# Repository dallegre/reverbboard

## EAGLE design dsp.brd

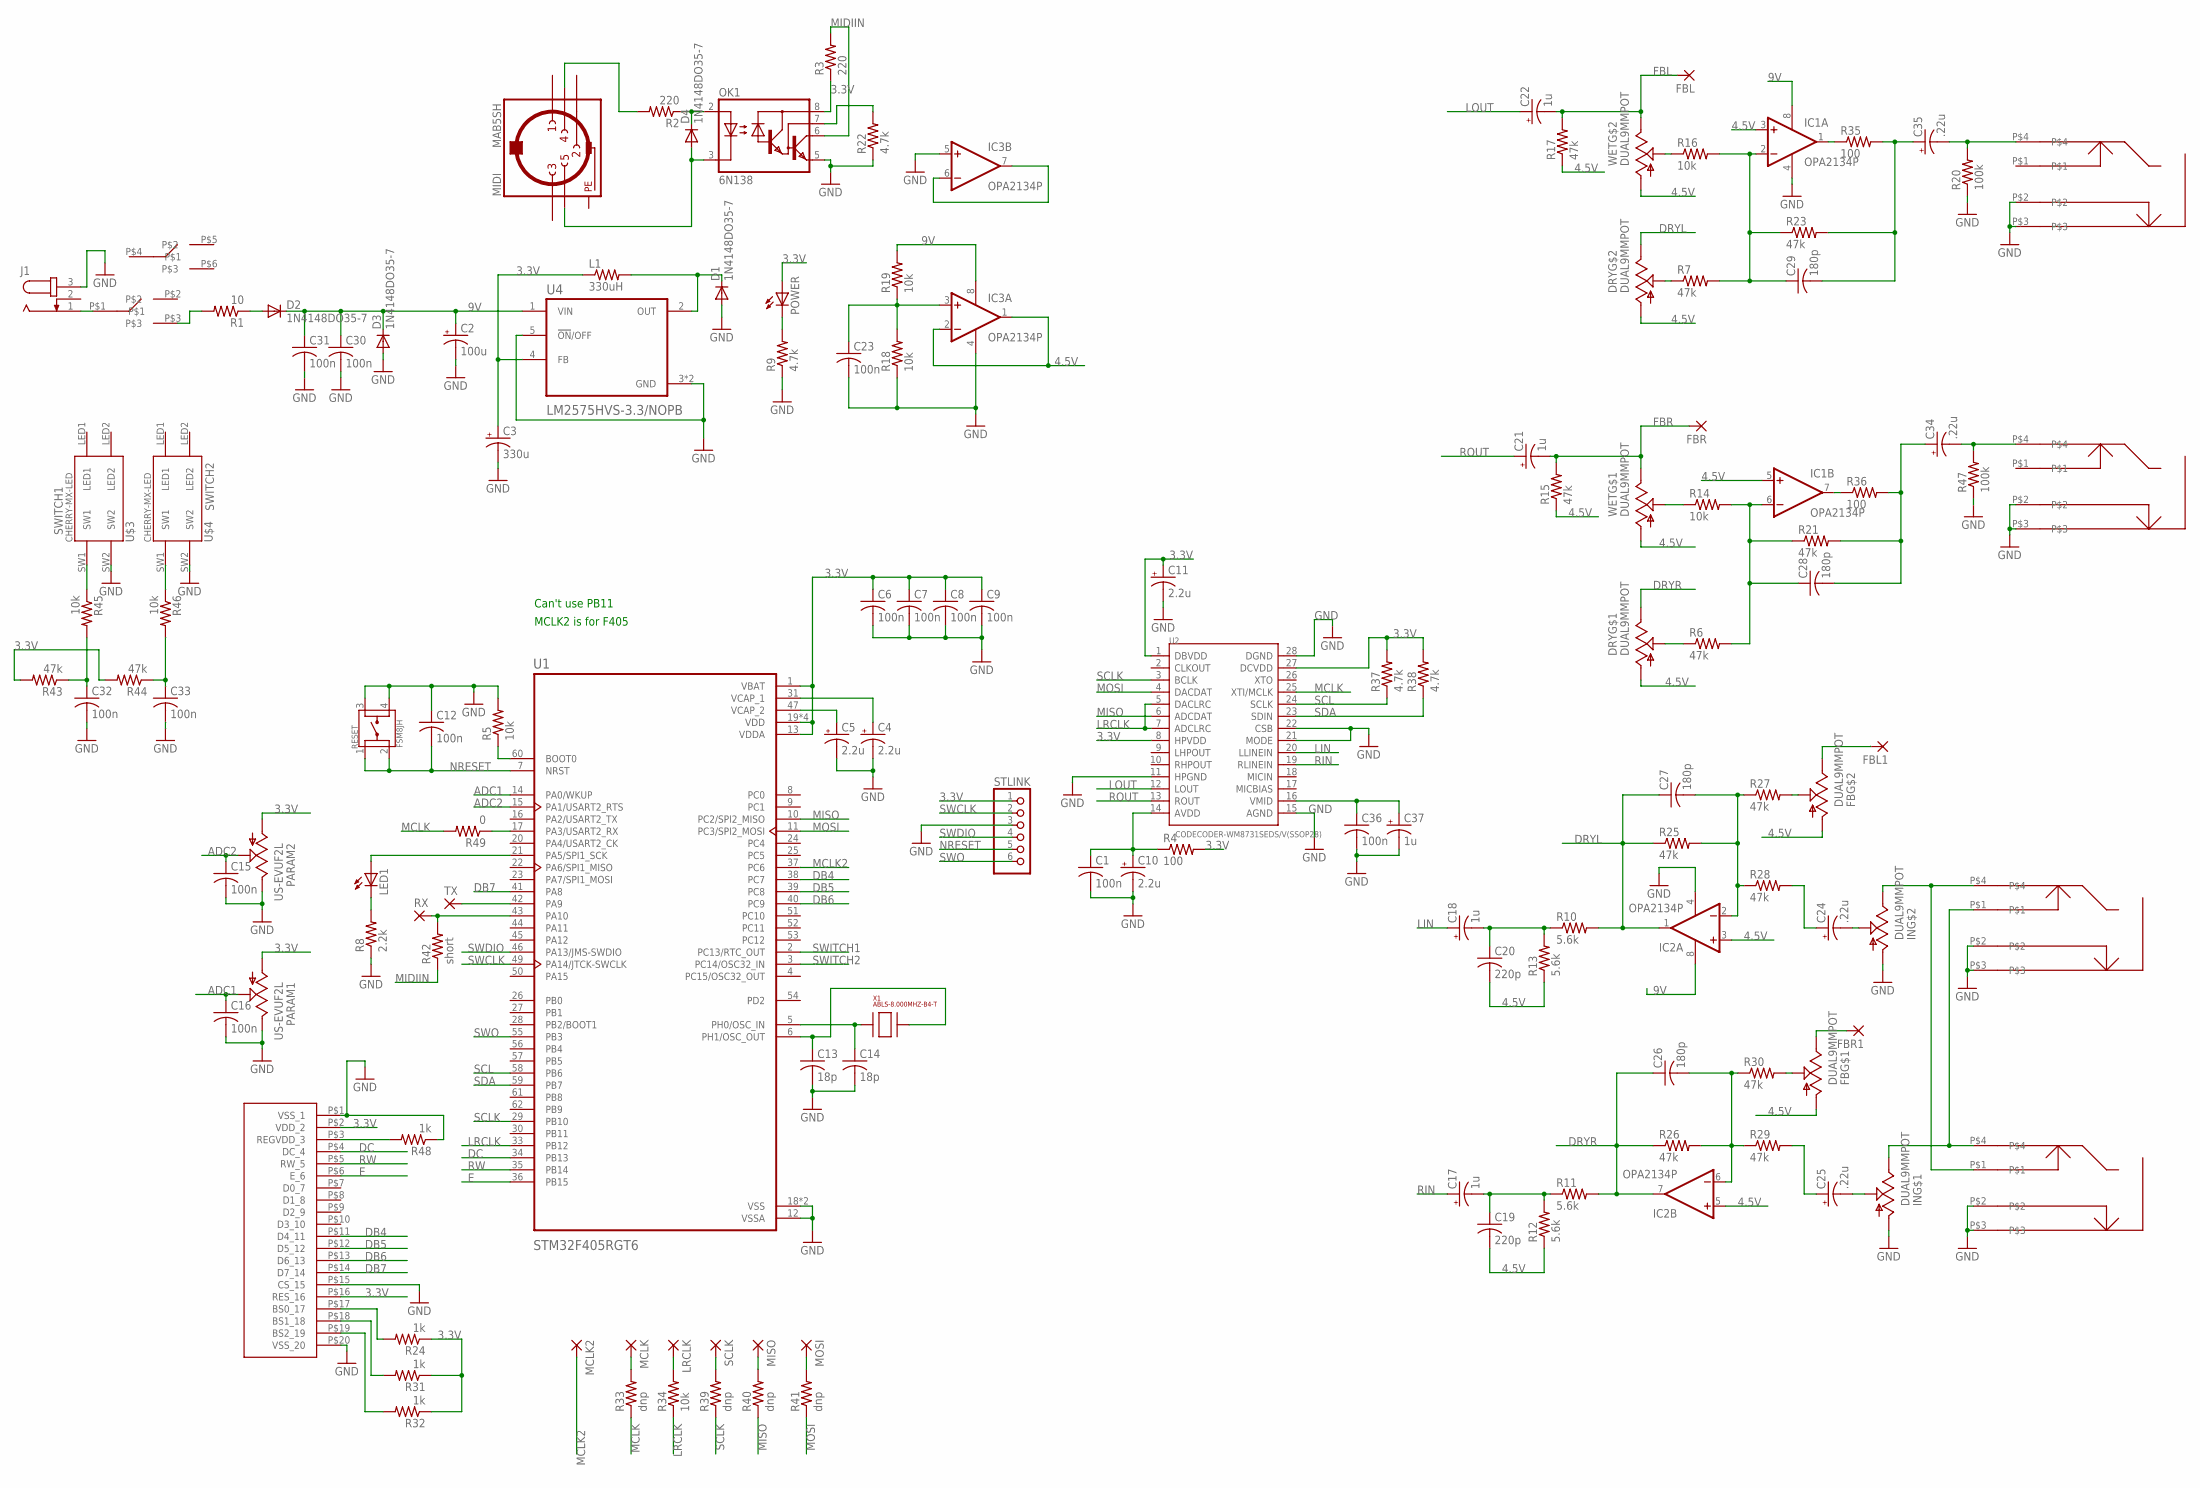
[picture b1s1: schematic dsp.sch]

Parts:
C1, C6, C7, C8, C9, C12, C15, C16, C23, C30, C31, C32, C33, C36: 100n; C050-025X075
C2: 100u; E2,5-7
C3: 330u; E3,5-8
C4, C5, C11: 2.2u; E2-4
C10: 2.2u; E2-5
C13, C14: 18p; C0603
C17, C18, C21, C22: 1u; E2,5-7
C19, C20: 220p; C050-025X075
C24, C25, C34, C35: .22u; E2,5-7
C26, C27, C28, C29: 180p; C050-025X075
C37: 1u; E2-4
D1, D2, D3, D4: 1N4148DO35-7; DO35-7
DRY: DUAL9MMPOT
FB: DUAL9MMPOT
FBL, FBL1: 2,0/0,9-S
FBR, FBR1: 2,0/0,9-S
IC1, IC2, IC3: OPA2134P; DIL08
IN: DUAL9MMPOT
INL: NMJ4HCD2
INR: NMJ4HCD2
J1: JACK-PLUG0; SPC4077
L1: 330uH; 0207/7
LED1: LED5MM
LRCLK: 2,0/0,9-S
MCLK, MCLK2: 2,0/0,9-S
MIDI: MAB5SH
MISO: 2,0/0,9-S
MOSI: 2,0/0,9-S
OK1: 6N138; DIL08
OUTL: NMJ4HCD2
OUTR: NMJ4HCD2
PARAM1, PARAM2: US-EVUF2L; EVUFXL
POWER: LED5MM
R1: 10; 0309V
R2, R3: 220; 0309V
R4, R35, R36: 100; 0309V
R5, R34: 10k; R0603
R6, R7, R15, R17, R21, R23, R25, R26, R27, R28, R29, R30, R43, R44: 47k; 0309V
R8: 2.2k; 0309V
R9, R22: 4.7k; 0309V
R10, R11, R12, R13: 5.6k; 0309V
R14, R16, R18, R19, R45, R46: 10k; 0309V
R20, R47: 100k; 0309V
R24, R31, R32, R48: 1k; 0309V
R33, R39, R40, R41: dnp; R0603
R37, R38: 4.7k; R0603
R42: short; 0309V
R49: 0; R0603
RESET: FSM8JH; SW_FSM8JH
RX: 2,0/0,9-S
SCLK: 2,0/0,9-S
STLINK: PINHD-1X6; 1X06
TX: 2,0/0,9-S
U1: STM32F405RGT6; QFP50P1200X1200X160-64N
U2: CODECODER-WM8731SEDS/V(SSOP28); SSOP28-0.65-10.2X5.2MM
U4: LM2575HVS-3.3/NOPB; VREG_TPS79625KTTR
U$1: NHD-0420CW
U$2: LC2255
U$3, U$4: CHERRY-MX-LED
WET: DUAL9MMPOT
X1: ABLS-8.000MHZ-B4-T; HC-49/US

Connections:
3.3V: C3.+, C6.1, C7.1, C8.1, C9.1, C11.+, L1.1, OK1.8 (VCC), PARAM1.1 (A), PARAM2.1 (A), POWER.A, R3.1, R4.2, R24.1, R31.1, R32.1, R37.2, R38.2, R43.2, R44.2, STLINK.1, U1.1 (VBAT), U1.13 (VDDA), U1.19 (VDD), U1.32 (VDD), U1.48 (VDD), U1.64 (VDD), U2.1 (DBVDD), U2.8 (HPVDD), U2.27 (DCVDD), U4.4 (FB), U$1.P$2 (VDD_2), U$1.P$16 (RES_16)
4.5V: C19.2, C20.2, DRY.1 (A), DRY.4 (A), FB.1 (A), FB.4 (A), IC1.3 (+IN), IC1.5 (+IN), IC2.3 (+IN), IC2.5 (+IN), IC3.1 (OUT), IC3.2 (-IN), R12.1, R13.1, R15.1, R17.1, WET.1 (A), WET.4 (A)
9V: C2.+, C30.1, C31.1, D2.C, D3.C, IC1.8 (V+), IC2.8 (V+), IC3.8 (V+), R19.2, U4.1 (VIN)
ADC1: C16.1, PARAM1.2 (S), U1.14 (PA0/WKUP)
ADC2: C15.1, PARAM2.2 (S), U1.15 (PA1/USART2_RTS)
DB4: U1.38 (PC7), U$1.P$11 (D4_11)
DB5: U1.39 (PC8), U$1.P$12 (D5_12)
DB6: U1.40 (PC9), U$1.P$13 (D6_13)
DB7: U1.41 (PA8), U$1.P$14 (D7_14)
DC: U1.34 (PB13), U$1.P$4 (DC_4)
DRYL: C27.1, DRY.6 (E), IC2.1 (OUT), R10.2, R25.1
DRYR: C26.1, DRY.3 (E), IC2.7 (OUT), R11.2, R26.1
E: U1.36 (PB15), U$1.P$6 (E_6)
FBL: C22.-, FBL.1, R17.2, WET.6 (E)
FBR: C21.-, FBR.1, R15.2, WET.3 (E)
GND: C1.2, C2.-, C3.-, C4.-, C5.-, C6.2, C7.2, C8.2, C9.2, C10.-, C11.-, C12.1, C13.2, C14.2, C15.2, C16.2, C23.2, C30.2, C31.2, C32.2, C33.2, C36.2, C37.-, D1.A, D3.A, IC1.4 (V-), IC2.4 (V-), IC3.4 (V-), IC3.5 (+IN), IN.1 (A), IN.4 (A), INL.P$2, INL.P$3, INR.P$2, INR.P$3, J1.3, OK1.5 (GND), OUTL.P$2, OUTL.P$3, OUTR.P$2, OUTR.P$3, PARAM1.3 (E), PARAM2.3 (E), R5.2, R8.1, R9.1, R18.1, R20.1, R22.1, R47.1, R48.1, RESET.3, RESET.4, STLINK.3, U1.12 (VSSA), U1.18 (VSS), U1.63 (VSS), U2.11 (HPGND), U2.15 (AGND), U2.21 (MODE), U2.22 (CSB), U2.28 (DGND), U4.3 (GND), U4.5 (!ON!/OFF), U4.6 (GND), U$1.P$1 (VSS_1), U$1.P$15 (CS_15), U$1.P$20 (VSS_20), U$3.SW2, U$4.SW2
LIN: C18.+, U2.20 (LLINEIN)
LOUT: C22.+, U2.12 (LOUT)
LRCLK: R34.1, U1.33 (PB12), U2.5 (DACLRC), U2.7 (ADCLRC)
MCLK: R33.1, R49.2, U2.25 (XTI/MCLK)
MCLK2: MCLK2.1, U1.37 (PC6)
MIDIIN: OK1.6 (VO), R3.2, R42.1
MISO: R40.1, U1.10 (PC2/SPI2_MISO), U2.6 (ADCDAT)
MOSI: R41.1, U1.11 (PC3/SPI2_MOSI), U2.4 (DACDAT)
unnamed: C4.+, U1.31 (VCAP_1)
unnamed: C5.+, U1.47 (VCAP_2)
unnamed: D2.A, R1.1
unnamed: D1.C, L1.2, U4.2 (OUT)
unnamed: C1.1, C10.+, R4.1, U2.14 (AVDD)
unnamed: R1.2, U$2.P$3
unnamed: R5.1, U1.60 (BOOT0)
unnamed: TX.1, U1.42 (PA9)
unnamed: LED1.A, U1.21 (PA5/SPI1_SCK)
unnamed: LED1.K (C), R8.2
unnamed: POWER.K (C), R9.2
unnamed: C13.1, U1.6 (PH1/OSC_OUT), X1.P$2 (3)
unnamed: C14.1, U1.5 (PH0/OSC_IN), X1.P$1 (1)
unnamed: FB.2 (S), R30.2
unnamed: C17.-, C19.1, R11.1, R12.2
unnamed: FB.5 (S), R27.2
unnamed: C18.-, C20.1, R10.1, R13.2
unnamed: C29.1, IC1.2 (-IN), R7.2, R16.2, R23.1
unnamed: C28.1, IC1.6 (-IN), R6.2, R14.2, R21.1
unnamed: C23.1, IC3.3 (+IN), R18.2, R19.1
unnamed: R14.1, WET.2 (S)
unnamed: R16.1, WET.5 (S)
unnamed: C28.2, C34.+, R21.2, R36.2
unnamed: C29.2, C35.+, R23.2, R35.2
unnamed: R49.1, U1.17 (PA3/USART2_RX)
unnamed: C24.+, R28.2
unnamed: C27.2, IC2.2 (-IN), R25.2, R27.1, R28.1
unnamed: C26.2, IC2.6 (-IN), R26.2, R29.1, R30.1
unnamed: IN.3 (E), INL.P$1, INR.P$4
unnamed: C25.+, R29.2
unnamed: IC1.7 (OUT), R36.1
unnamed: IC1.1 (OUT), R35.1
unnamed: C24.-, IN.5 (S)
unnamed: C25.-, IN.2 (S)
unnamed: DRY.2 (S), R6.1
unnamed: DRY.5 (S), R7.1
unnamed: J1.1, U$2.P$1
unnamed: OK1.7 (VB), R22.2
unnamed: D4.C, OK1.2 (A), R2.1
unnamed: MIDI.4, R2.2
unnamed: D4.A, MIDI.5, OK1.3 (C)
unnamed: R32.2, U$1.P$19 (BS2_19)
unnamed: R31.2, U$1.P$18 (BS1_18)
unnamed: R24.2, U$1.P$17 (BS0_17)
unnamed: MCLK.1, R33.2
unnamed: LRCLK.1, R34.2
unnamed: R39.2, SCLK.1
unnamed: MISO.1, R40.2
unnamed: MOSI.1, R41.2
unnamed: R42.2, RX.1, U1.43 (PA10)
unnamed: R45.1, U$3.SW1
unnamed: R46.1, U$4.SW1
unnamed: C35.-, OUTL.P$4, R20.2
unnamed: C34.-, OUTR.P$4, R47.2
unnamed: FB.6 (E), FBL1.1
unnamed: FB.3 (E), FBR1.1
unnamed: C36.1, C37.+, U2.16 (VMID)
unnamed: IN.6 (E), INL.P$4, INR.P$1
unnamed: R48.2, U$1.P$3 (REGVDD_3)
unnamed: IC3.6 (-IN), IC3.7 (OUT)
NRESET: C12.2, RESET.1, RESET.2, STLINK.5, U1.7 (NRST)
PE: MIDI.PE, MIDI.PE@ (PE)
RIN: C17.+, U2.19 (RLINEIN)
ROUT: C21.+, U2.13 (ROUT)
RW: U1.35 (PB14), U$1.P$5 (RW_5)
SCL: R37.1, U1.58 (PB6), U2.24 (SCLK)
SCLK: R39.1, U1.29 (PB10), U2.3 (BCLK)
SDA: R38.1, U1.59 (PB7), U2.23 (SDIN)
SWCLK: STLINK.2, U1.49 (PA14/JTCK-SWCLK)
SWDIO: STLINK.4, U1.46 (PA13/JMS-SWDIO)
SWITCH1: C32.1, R43.1, R45.2, U1.2 (PC13/RTC_OUT)
SWITCH2: C33.1, R44.1, R46.2, U1.3 (PC14/OSC32_IN)
SWO: STLINK.6, U1.55 (PB3)

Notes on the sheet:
Can't use PB11
MCLK2 is for F405

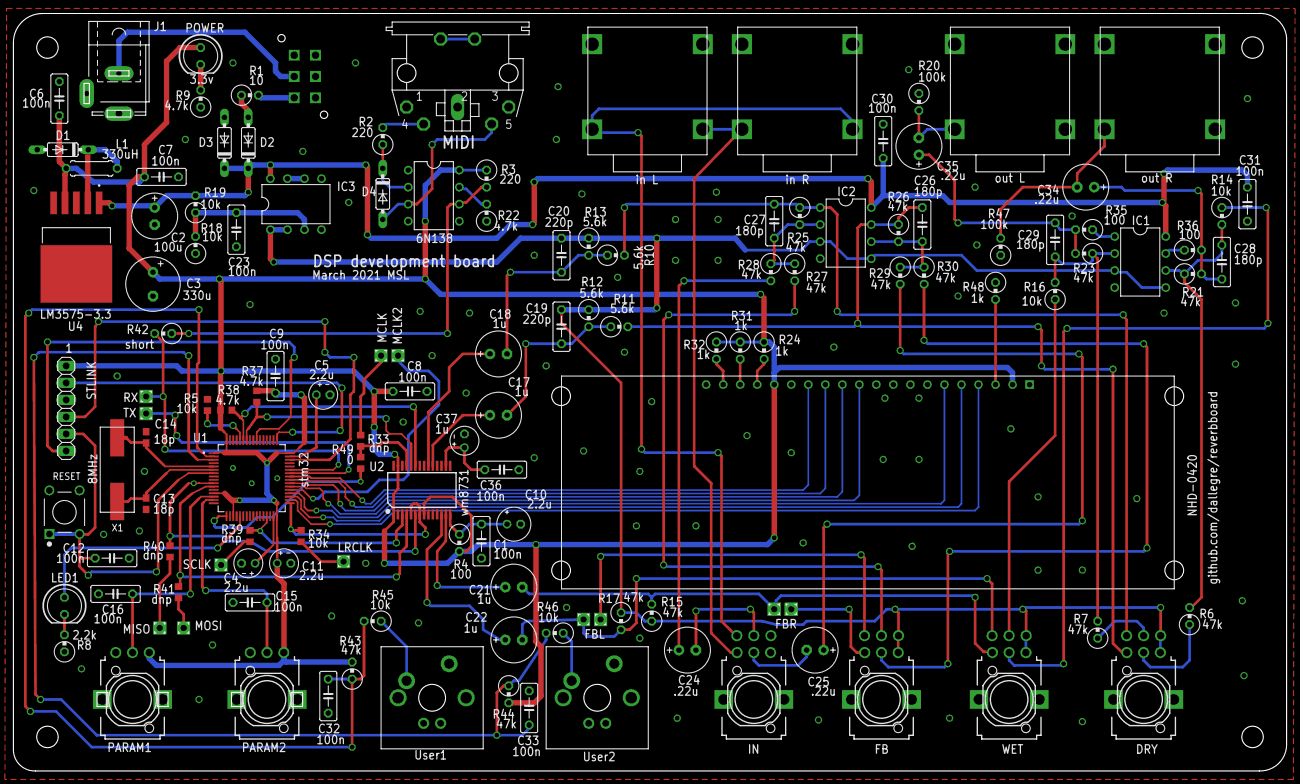
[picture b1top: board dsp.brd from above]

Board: 2 copper layers, 190.0 x 113.0 mm, 131 parts (0 on the bottom side), 97 nets.

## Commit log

2021-03-08 fixed mclk and uart connections
2021-03-08 changed virtual ground to an op amp buffer
2021-03-08 mono routing, ac coupled op, jumper for feedback
2021-03-08 routing for mono on both inputs
2021-03-08 connected mode and csb on wm8731
2021-03-09 added a ground for vccref and moved icp header to edge
2021-03-10 added a mclk optin for pc6 for f405 compatibility
2021-03-10 sent it out to get made
2021-03-25 fixed grounds problem on codec (post fab)
2021-03-25 updated mixer resistors for higher wet amplitude
